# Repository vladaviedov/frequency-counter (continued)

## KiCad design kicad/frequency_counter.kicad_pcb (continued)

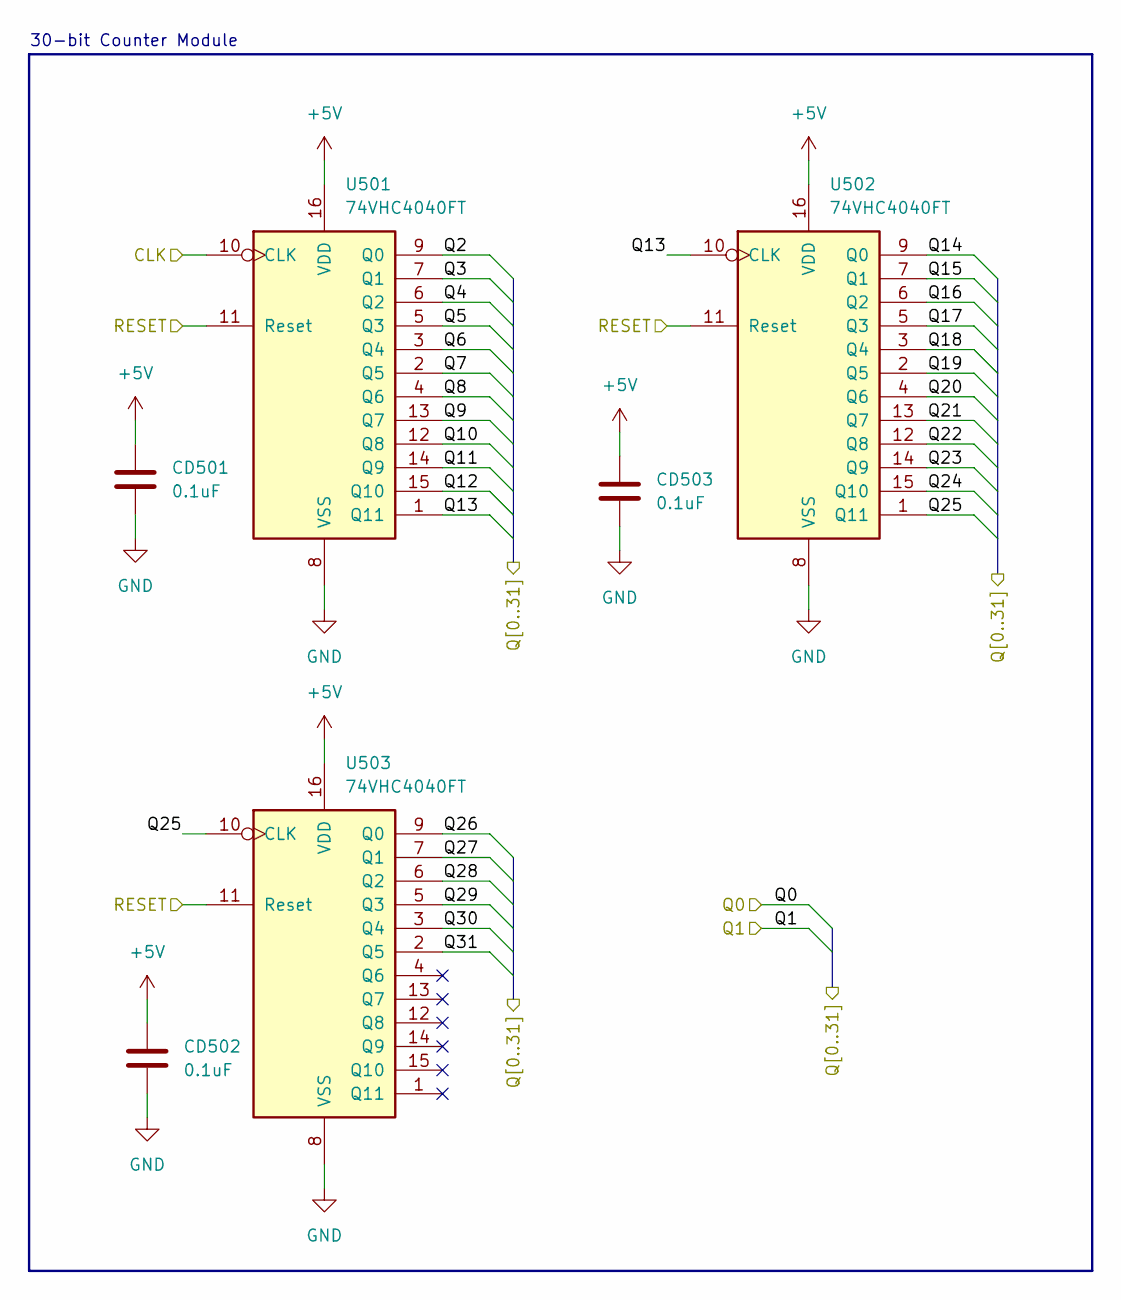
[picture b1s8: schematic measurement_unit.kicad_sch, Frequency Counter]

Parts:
CD501, CD502, CD503: 0.1uF; C_0402_1005Metric_Fix; MPN KGM05AR51C104KH
U501, U502, U503: 74VHC4040FT; TSSOP-16_4.4x5mm_P0.65mm; MPN 74VHC4040FT

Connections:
+5V: CD501.1, CD502.1, CD503.1, U501.16 (VDD), U502.16 (VDD), U503.16 (VDD); also elsewhere on the board
/Channel Gate/MU_CLK: U501.10 (CLK); also elsewhere on the board
/Measurement Unit/Q2: U501.9 (Q0); also elsewhere on the board
/Measurement Unit/Q3: U501.7 (Q1); also elsewhere on the board
/Measurement Unit/Q4: U501.6 (Q2); also elsewhere on the board
/Measurement Unit/Q5: U501.5 (Q3); also elsewhere on the board
/Measurement Unit/Q6: U501.3 (Q4); also elsewhere on the board
/Measurement Unit/Q7: U501.2 (Q5); also elsewhere on the board
/Measurement Unit/Q8: U501.4 (Q6); also elsewhere on the board
/Measurement Unit/Q9: U501.13 (Q7); also elsewhere on the board
/Measurement Unit/Q10: U501.12 (Q8); also elsewhere on the board
/Measurement Unit/Q11: U501.14 (Q9); also elsewhere on the board
/Measurement Unit/Q12: U501.15 (Q10); also elsewhere on the board
/Measurement Unit/Q13: U501.1 (Q11), U502.10 (CLK); also elsewhere on the board
/Measurement Unit/Q14: U502.9 (Q0); also elsewhere on the board
/Measurement Unit/Q15: U502.7 (Q1); also elsewhere on the board
/Measurement Unit/Q16: U502.6 (Q2); also elsewhere on the board
/Measurement Unit/Q17: U502.5 (Q3); also elsewhere on the board
/Measurement Unit/Q18: U502.3 (Q4); also elsewhere on the board
/Measurement Unit/Q19: U502.2 (Q5); also elsewhere on the board
/Measurement Unit/Q20: U502.4 (Q6); also elsewhere on the board
/Measurement Unit/Q21: U502.13 (Q7); also elsewhere on the board
/Measurement Unit/Q22: U502.12 (Q8); also elsewhere on the board
/Measurement Unit/Q23: U502.14 (Q9); also elsewhere on the board
/Measurement Unit/Q24: U502.15 (Q10); also elsewhere on the board
/Measurement Unit/Q25: U502.1 (Q11), U503.10 (CLK); also elsewhere on the board
/Measurement Unit/Q26: U503.9 (Q0); also elsewhere on the board
/Measurement Unit/Q27: U503.7 (Q1); also elsewhere on the board
/Measurement Unit/Q28: U503.6 (Q2); also elsewhere on the board
/Measurement Unit/Q29: U503.5 (Q3); also elsewhere on the board
/Measurement Unit/Q30: U503.3 (Q4); also elsewhere on the board
/Measurement Unit/Q31: U503.2 (Q5); also elsewhere on the board
/Measurement Unit/RESET: U501.11 (Reset), U502.11 (Reset), U503.11 (Reset); also elsewhere on the board
GND: CD501.2, CD502.2, CD503.2, U501.8 (VSS), U502.8 (VSS), U503.8 (VSS); also elsewhere on the board

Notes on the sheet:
30-bit Counter Module

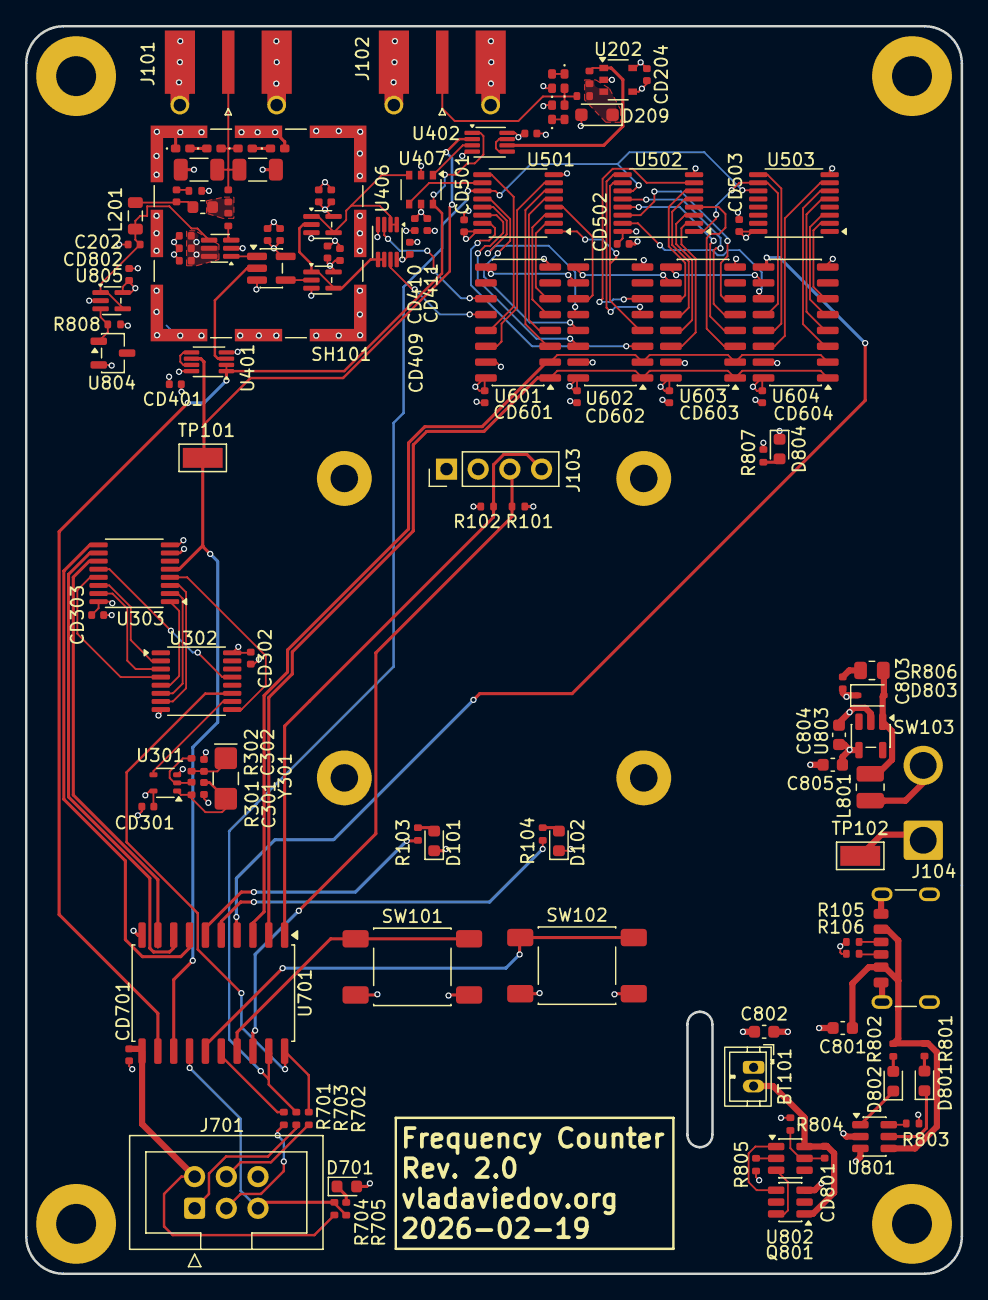
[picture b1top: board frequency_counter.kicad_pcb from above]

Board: 4 copper layers, 75.0 x 100.0 mm, 131 parts (0 on the bottom side), 114 nets.

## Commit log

2025-12-25 add design files for rev 1.0
2025-12-25 add pcb release for rev 1.0
2025-12-25 add license & readme
2025-12-25 add firmware submodule
2025-12-25 ff firmware
2025-12-26 rework isp header, update pinout
2025-12-26 add i2c pullups, fix power switch + tp, update block
2026-02-17 redesign pierce oscillator
2026-02-17 split frontend into two channels
2026-02-17 swap encoder for two buttons, assign channel select pin
2026-02-18 ch a voltage reference, ch b hysteresis
2026-02-18 rework frontend, channel gating
2026-02-18 replace alum caps with ceramics, change mpn labeling
2026-02-19 finish 2.0 part selection
2026-02-19 assign references
2026-02-19 minor fixes, 2.0 schematic
2026-02-19 redesign pcb for 2.0
